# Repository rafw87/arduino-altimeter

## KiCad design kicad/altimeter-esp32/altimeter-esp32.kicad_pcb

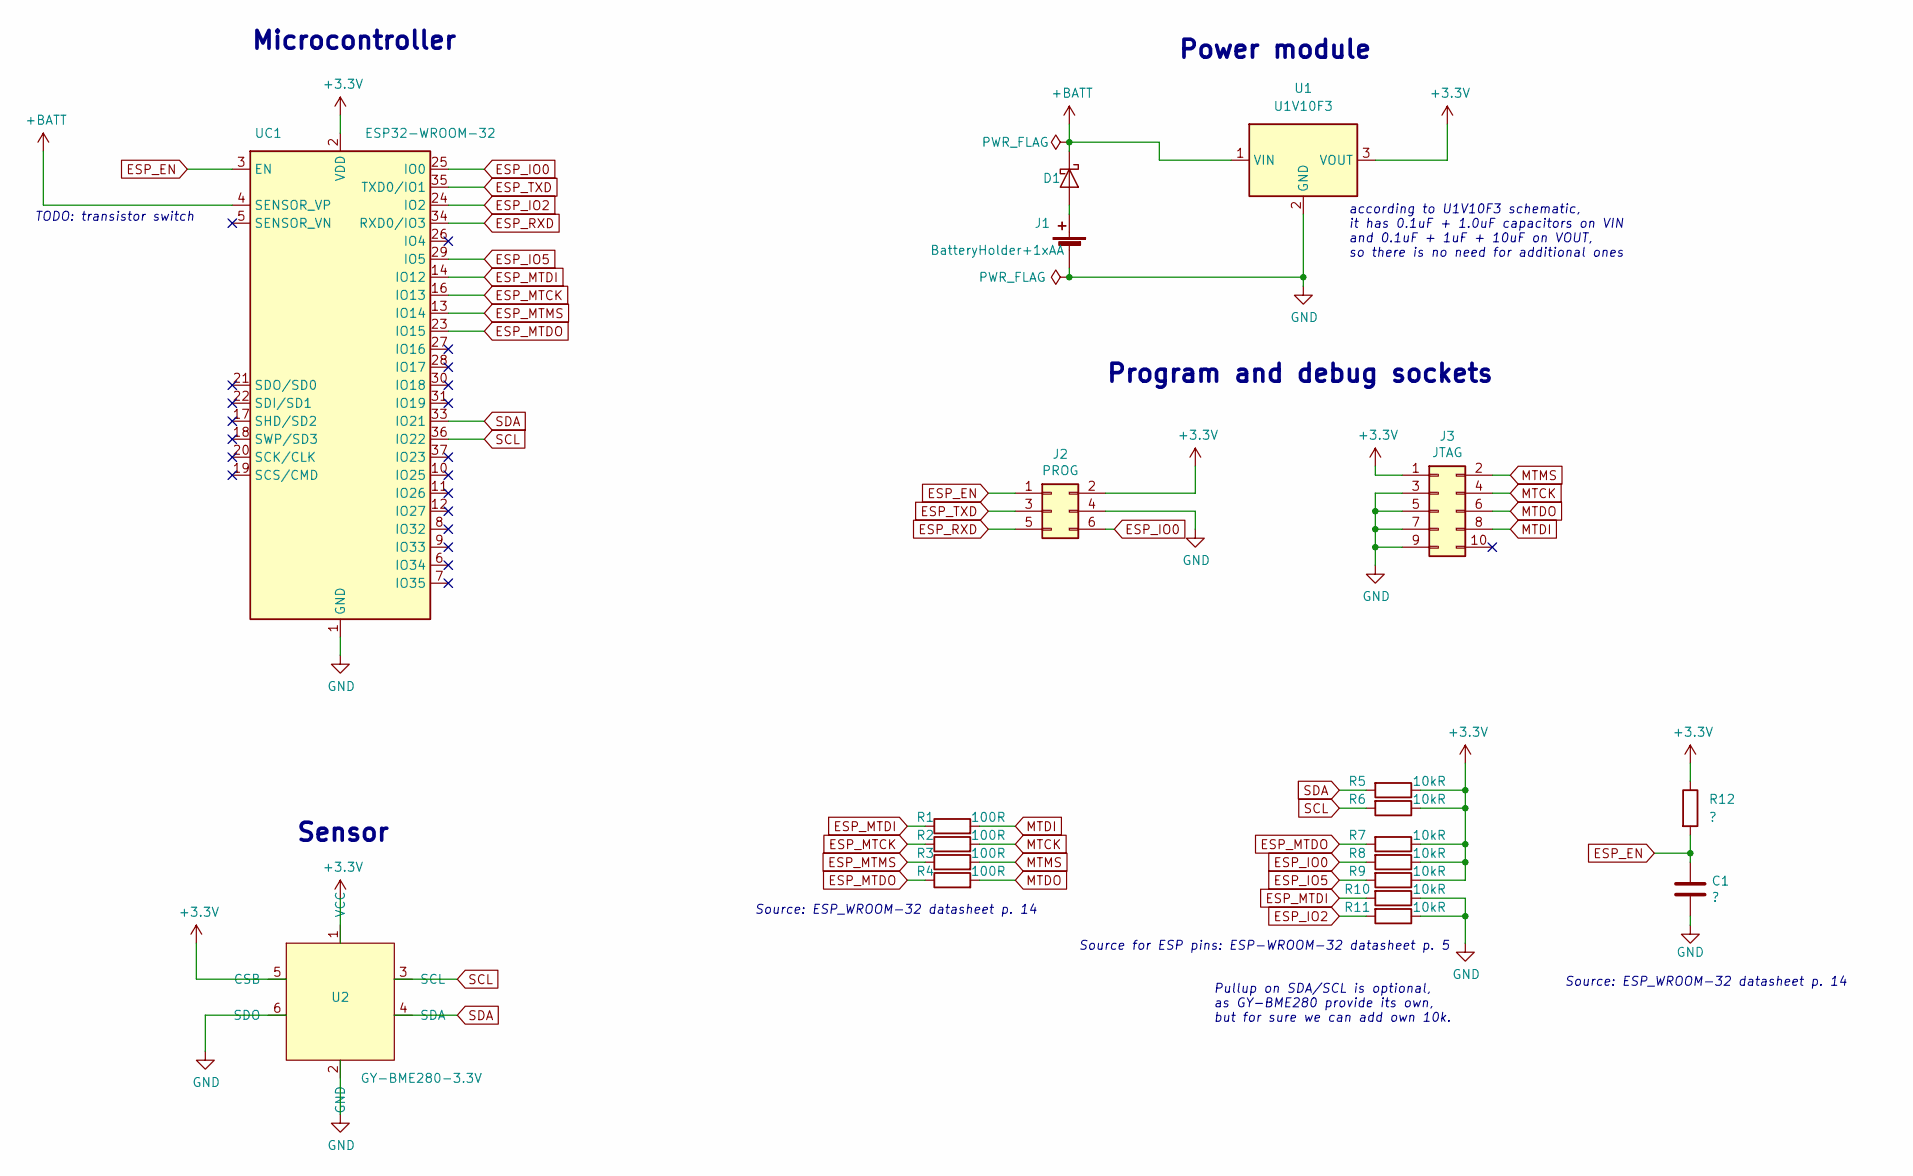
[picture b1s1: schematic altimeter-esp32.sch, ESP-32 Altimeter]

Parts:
C1: ?; C_Disc_D3.0mm_W1.6mm_P2.50mm
D1: D_Schottky; D_DO-35_SOD27_P10.16mm_Horizontal
J1: BatteryHolder+1xAA; BatteryHolder_Keystone_2460_1xAA
J2: PROG; IDC-Header_2x03_P2.54mm_Vertical
J3: JTAG; IDC-Header_2x05_P2.54mm_Vertical
R1, R2, R3, R4: 100R; R_Axial_DIN0204_L3.6mm_D1.6mm_P7.62mm_Horizontal
R5, R6, R7, R8, R9, R10, R11: 10kR; R_Axial_DIN0204_L3.6mm_D1.6mm_P7.62mm_Horizontal
R12: ?; R_Axial_DIN0204_L3.6mm_D1.6mm_P7.62mm_Horizontal
U1: U1V10F3; Converter_DCDC_Pololu_U1V5Fx_Vertical
U2: GY-BME280-3.3V; BME-280-3.3v-Horizontal
UC1: ESP32-WROOM-32

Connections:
+3V3: J2.2, J3.1, R5.1, R6.1, R7.1, R8.1, R9.1, R12.1, U1.3 (VOUT), U2.1 (VCC), U2.5 (CSB), UC1.2 (VDD)
+BATT: D1.1 (K), U1.1 (VIN), UC1.4 (SENSOR_VP)
ESP_EN: C1.2, J2.1, R12.2, UC1.3 (EN)
ESP_IO0: J2.6, R8.2, UC1.25 (IO0)
ESP_IO2: R11.2, UC1.24 (IO2)
ESP_IO5: R9.2, UC1.29 (IO5)
ESP_MTCK: R2.1, UC1.16 (IO13)
ESP_MTDI: R1.1, R10.2, UC1.14 (IO12)
ESP_MTDO: R4.1, R7.2, UC1.23 (IO15)
ESP_MTMS: R3.1, UC1.13 (IO14)
ESP_RXD: J2.5, UC1.34 (RXD0/IO3)
ESP_TXD: J2.3, UC1.35 (TXD0/IO1)
GND: C1.1, J1.2 (-), J2.4, J3.3, J3.5, J3.7, J3.9, R10.1, R11.1, U1.2 (GND), U2.2 (GND), U2.6 (SDO), UC1.1 (GND), UC1.15 (GND), UC1.38 (GND), UC1.39 (GND)
MTCK: J3.4, R2.2
MTDI: J3.8, R1.2
MTDO: J3.6, R4.2
MTMS: J3.2, R3.2
unnamed: D1.2 (A), J1.1 (+)
SCL: R6.2, U2.3 (SCL), UC1.36 (IO22)
SDA: R5.2, U2.4 (SDA), UC1.33 (IO21)

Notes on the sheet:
Microcontroller
Program and debug sockets
Power module
Sensor
according to U1V10F3 schematic, it has 0.1uF + 1.0uF capacitors on VIN and 0.1uF + 1uF + 10uF on VOUT, so there is no need for additional ones
Source for ESP pins: ESP-WROOM-32 datasheet p. 5
Source: ESP_WROOM-32 datasheet p. 14
Pullup on SDA/SCL is optional, as GY-BME280 provide its own, but for sure we can add own 10k.
TODO: transistor switch

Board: 2 copper layers, 20 parts (0 on the bottom side), 20 nets, no tracks yet.

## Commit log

2020-08-30 chore(mobile): initial React Native commit
2020-08-30 chore(mobile): switch to TypeScript
2020-08-30 chore(arduino): add empty sketch
2020-08-30 feat(arduino): add sensor + battery status
2020-08-30 feat(mobile): configure Prettier
2020-08-30 feat(fritzing): add sketch for evaluation board
2020-08-30 feat(mobile): add fake measurements
2020-08-30 refactor(arduino): refactor
2020-08-30 feat(arduino): add bluetooth support
2020-08-30 refactor(mobile): replace AltitudeDisplay by generic MeasurementDisplay
2020-09-08 refactor(arduino): extract BME280 handling to separate file
2020-09-08 feat(mobile): add Bluetooth connection status
2020-09-08 refactor(mobile): Add Redux and RxJS
2020-09-08 refactor(arduino): extract BLE to separate file
2020-09-08 feat(mobile): add real bluetooth integration
2020-09-08 refactor(mobile): refactor services
2020-09-08 refactor(arduino): extract measurements calculation to separate file
2020-09-08 refactor(arduino): use BLE.poll()
2020-09-08 feat(mobile): [UNSTABLE] add restore state functionality + reconnect
2020-09-08 feat(arduino): add BatterySevice
2020-09-08 chore(mobile): specify path in tsconfig.json
2020-09-08 test(mobile): add MiBandBluetoothService for testing connection
2020-09-08 style(arduino): reformat code with CLion
2020-09-08 chore(arduino): switch project to PlatformIO
2020-09-08 refactor(arduino): fix warnings
2020-09-08 refactor(arduino): move sources to .cpp files
2020-09-08 refactor(arduino): extract BLE constants to separate file
2020-09-08 feat: add Reset functionality
2020-09-08 feat: add Reset functionality - changed from 3 clicks to click & confirm
2020-09-08 fix(arduino): fixes for BLE
    1. .poll() always wait for provided time
    2. workaround? for disconnecting issue
2020-09-08 feat(arduino): add EEPROM support
2020-09-08 feat(mobile): add decimal points to measurements
2020-09-08 feat(mobile): buffer measurement change actions in service
2020-09-08 style(arduino): fix warnings
2020-09-08 refactor(arduino): read/write methods of EEPROM receiving value by ref
2020-09-08 fix(mobile): fix for edit mode
    Draft value stored as string.
2020-09-08 feat(arduino): add factory reset
    Activated with 10-13 seconds of LOW state on D12 pin.
2020-09-08 fix(arduino): do not reset sea level pressure
2020-09-09 fix(arduino): optional hotfix for reconnection problem
    Restart after disconnect (if PIN 11 is LOW)
2020-09-09 feat(arduino): display connection status on build-in RGB LED
2020-09-09 fix(mobile): add battery level and reading
2020-09-13 fix(arduino): tune battery level constants and altitude hysteresis
2020-09-13 feat(arduino): implement moving average for altitude and battery
2020-09-13 fix(mobile): improve layout and decimal places
2020-09-14 feat(documentation): add KiCAD schematics for ESP32 based altimeter
2020-09-14 feat(documentation): add exported schematics
